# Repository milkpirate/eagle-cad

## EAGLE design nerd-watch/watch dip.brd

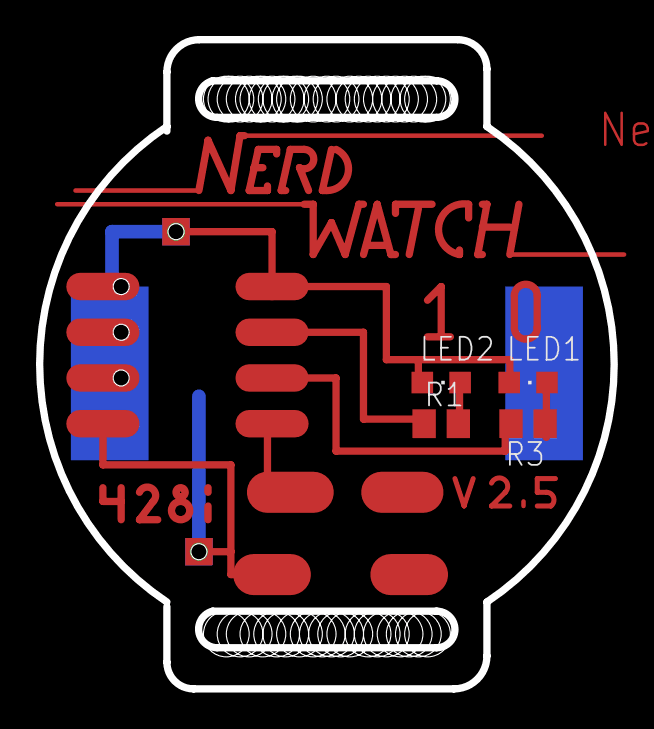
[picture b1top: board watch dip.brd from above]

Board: 2 copper layers, 31.9 x 36.1 mm, 4 parts (0 on the bottom side), 3 nets.

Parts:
LED1, LED2: CHIPLED_0805
R1, R3: M0805

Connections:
3.3V: LED1.A, LED2.A
unnamed: LED2.C, R1.2
unnamed: LED1.C, R3.2

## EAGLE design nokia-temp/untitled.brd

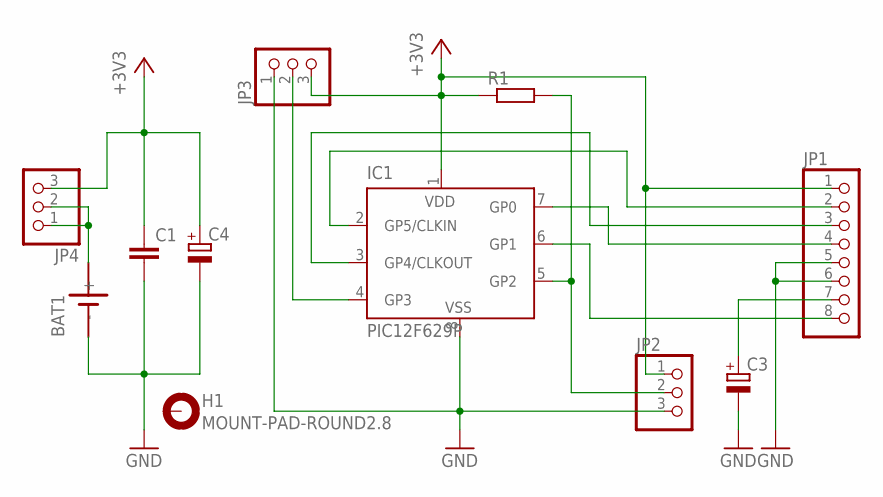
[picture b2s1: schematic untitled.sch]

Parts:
BAT1: SN2032
C1: C-EU025-025X050; C025-025X050
C3, C4: CPOL-EUTT2D5L; TT2D5L
H1: MOUNT-PAD-ROUND2.8; 2,8-PAD
IC1: PIC12F629P; DIL8
JP1: PINHD-1X8; 1X08
JP2, JP3, JP4: PINHD-1X3; 1X03
R1: R-EU_0204/2V; 0204V

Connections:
+3V3: C1.1, C4.+, IC1.1 (VDD), JP1.1, JP2.1, JP3.3, JP4.3, R1.1
GND: BAT1.-, C1.2, C3.-, C4.-, IC1.8 (VSS), JP1.5, JP1.6, JP2.3, JP3.1
unnamed: IC1.6 (GP1), JP1.8
unnamed: IC1.7 (GP0), JP1.4
unnamed: IC1.2 (GP5/CLKIN), JP1.2
unnamed: IC1.3 (GP4/CLKOUT), JP1.3
unnamed: IC1.4 (GP3), JP3.2
unnamed: BAT1.+, JP4.1, JP4.2
unnamed: C3.+, JP1.7
unnamed: IC1.5 (GP2), JP2.2, R1.2

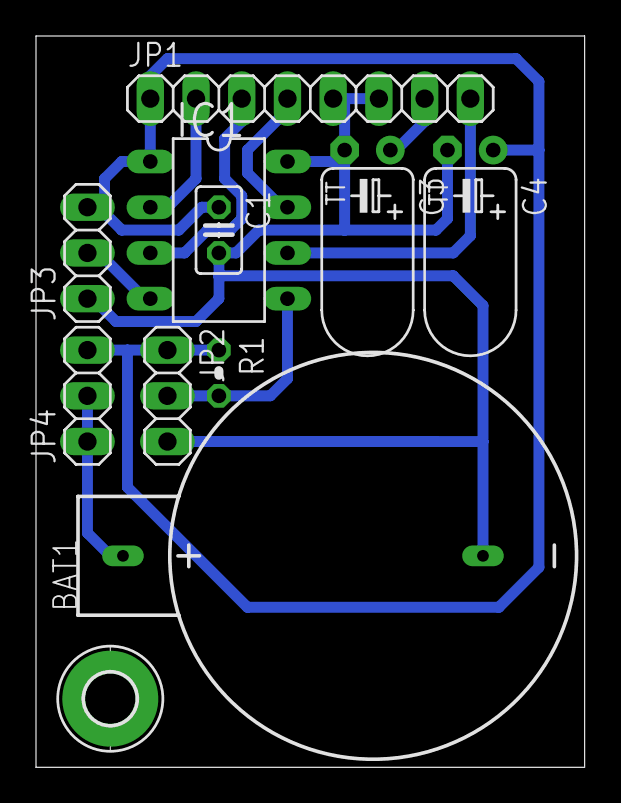
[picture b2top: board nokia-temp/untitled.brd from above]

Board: 2 copper layers, 30.5 x 40.6 mm, 11 parts (0 on the bottom side), 10 nets.

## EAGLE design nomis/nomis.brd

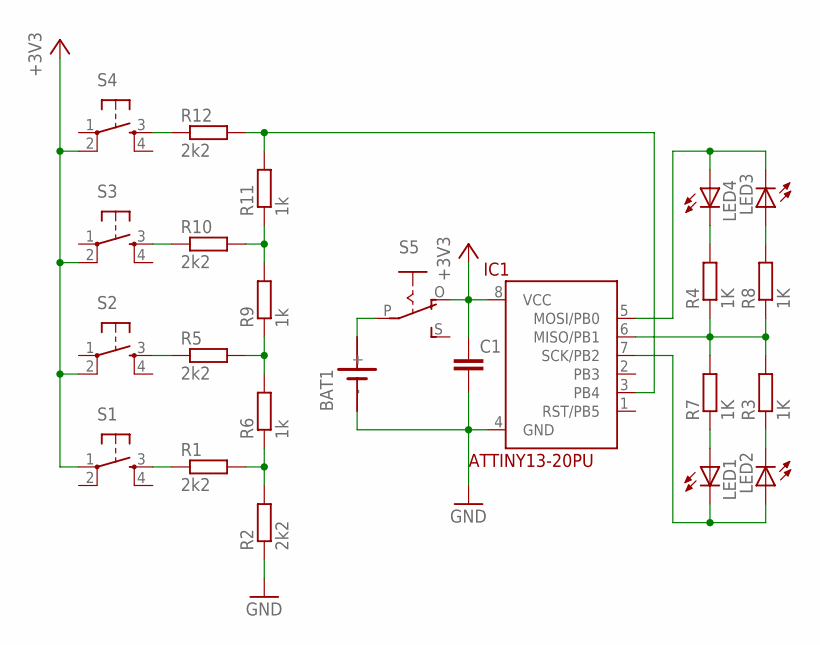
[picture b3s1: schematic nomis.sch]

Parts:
BAT1: SN2032
C1: C-EU025-025X050; C025-025X050
IC1: ATTINY13-20PU; DIL08
LED1, LED2, LED3, LED4: LED5MM
R1, R2, R5, R10, R12: 2k2; 0207/7
R3, R4, R7, R8: 1K; 0207/7
R6, R9, R11: 1k; 0207/7
S1, S2, S3, S4: TAC_SWITCHPTH; TACTILE-PTH
S5: EG1218S; EG1218

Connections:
+3V3: C1.1, IC1.8 (VCC), S1.1, S2.2, S3.2, S4.2, S5.O
GND: BAT1.-, C1.2, IC1.4 (GND), R2.1
unnamed: R10.1, S3.3
unnamed: R5.1, S2.3
unnamed: BAT1.+, S5.P
unnamed: LED2.K (C), R3.1
unnamed: LED4.K (C), R4.2
unnamed: LED1.A, R7.1
unnamed: IC1.6 (MISO/PB1), R3.2, R4.1, R7.2, R8.1
unnamed: IC1.7 (SCK/PB2), LED1.K (C), LED2.A
unnamed: IC1.5 (MOSI/PB0), LED3.K (C), LED4.A
unnamed: LED3.A, R8.2
unnamed: R12.1, S4.3
unnamed: IC1.3 (PB4), R11.2, R12.2
unnamed: R9.2, R10.2, R11.1
unnamed: R5.2, R6.2, R9.1
unnamed: R1.2, R2.2, R6.1
unnamed: R1.1, S1.3

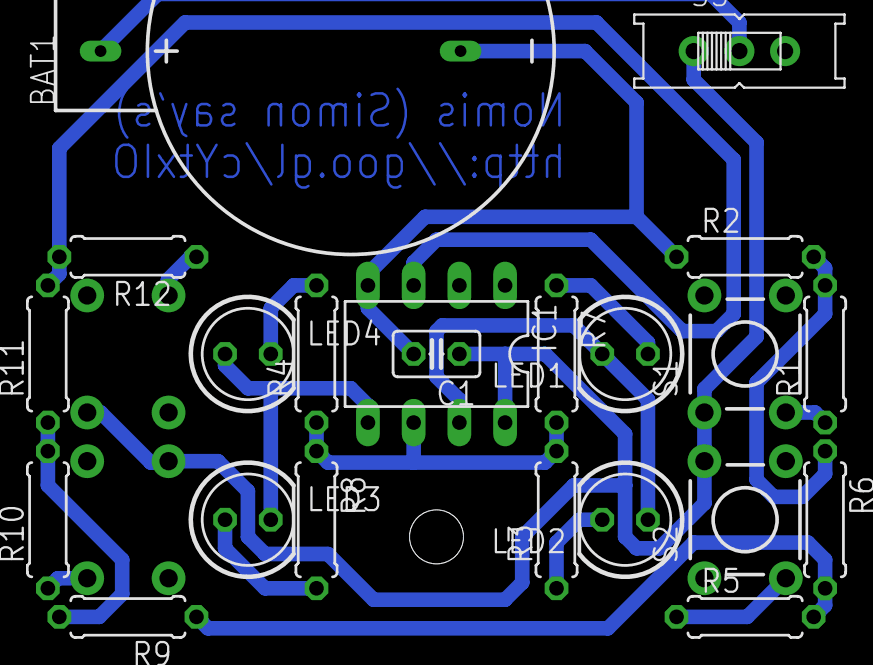
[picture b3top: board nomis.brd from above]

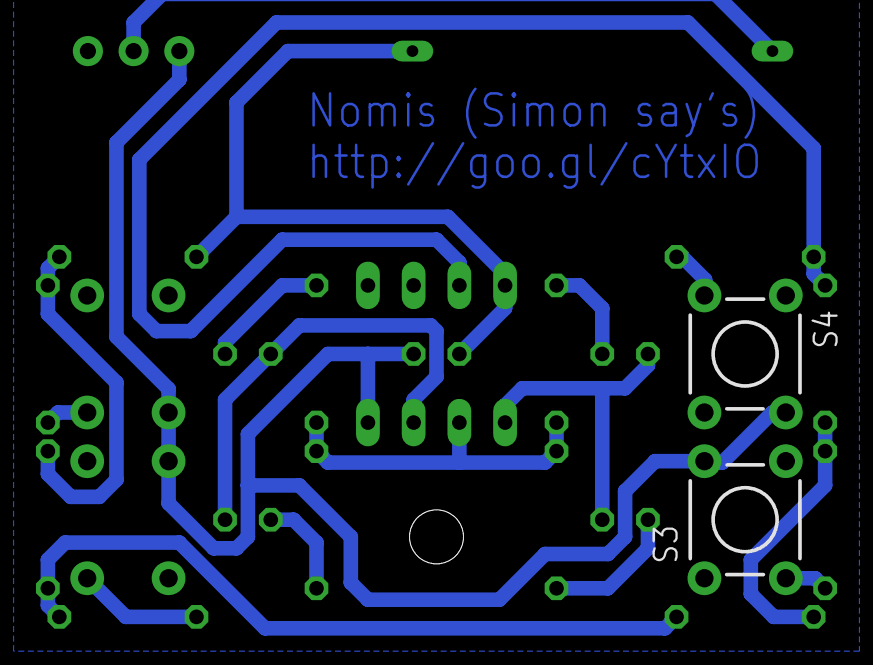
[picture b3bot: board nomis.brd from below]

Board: 2 copper layers, 24 parts (2 on the bottom side), 18 nets.

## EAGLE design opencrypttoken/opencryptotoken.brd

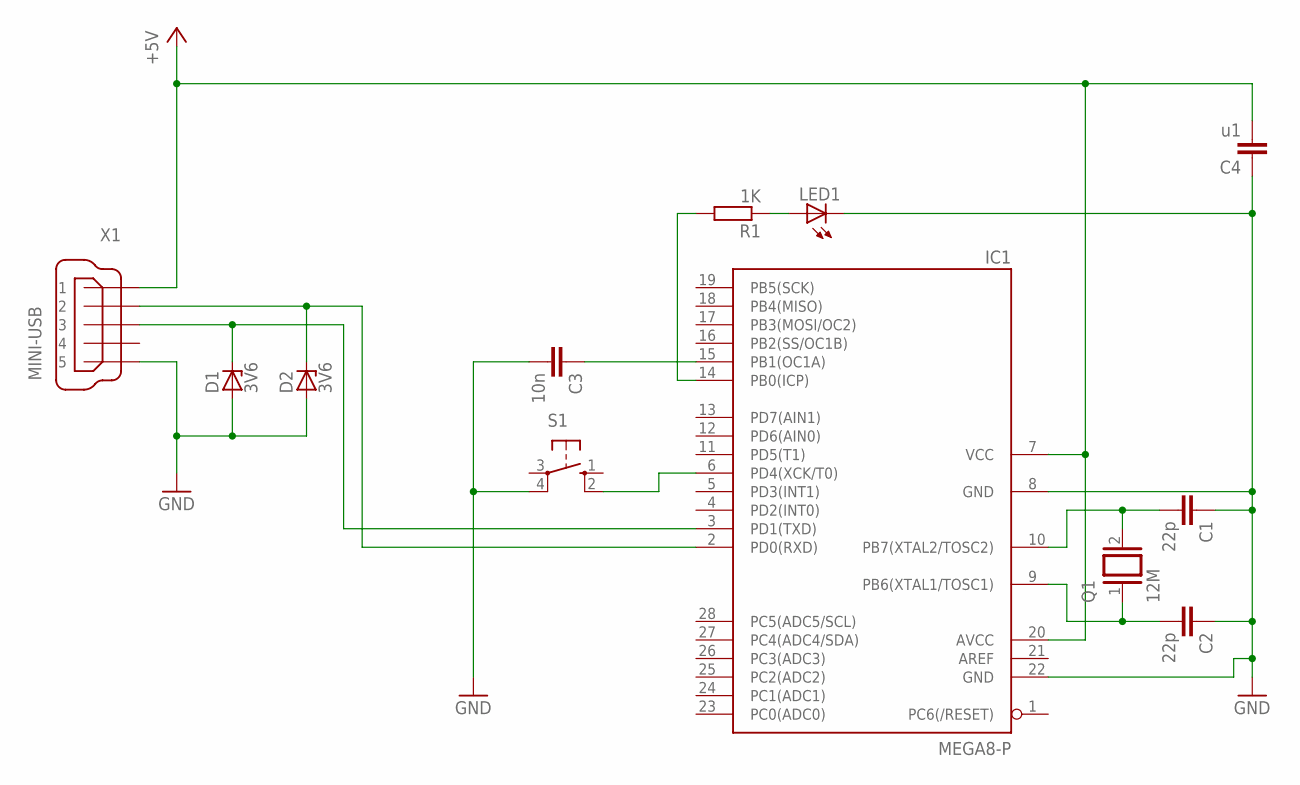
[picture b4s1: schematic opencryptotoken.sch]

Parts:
C1, C2: 22p; C025-024X044
C3: 10n; C025-024X044
C4: u1; C025-024X044
D1: 3V6; ZDIO-2.5
D2: 3V6; ZDIO-5
IC1: MEGA8-P; DIL28-3
LED1: LED5MM
Q1: 12M; QS
R1: 1K; 0204V
S1: 10-XX; B3F-10XX
X1: MINI-USB; 32005-601

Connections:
+5V: C4.2, IC1.7 (VCC), IC1.20 (AVCC), X1.1
GND: C1.1, C2.1, C3.2, C4.1, D1.A, D2.A, IC1.8 (GND), IC1.22 (GND), LED1.K (C), S1.4 (P1), X1.5
unnamed: C1.2, IC1.10 (PB7(XTAL2/TOSC2)), Q1.2
unnamed: C2.2, IC1.9 (PB6(XTAL1/TOSC1)), Q1.1
unnamed: C3.1, IC1.15 (PB1(OC1A))
unnamed: IC1.14 (PB0(ICP)), R1.2
unnamed: LED1.A, R1.1
unnamed: D2.C, IC1.2 (PD0(RXD)), X1.2
unnamed: D1.C, IC1.3 (PD1(TXD)), X1.3
unnamed: IC1.6 (PD4(XCK/T0)), S1.2 (S1)

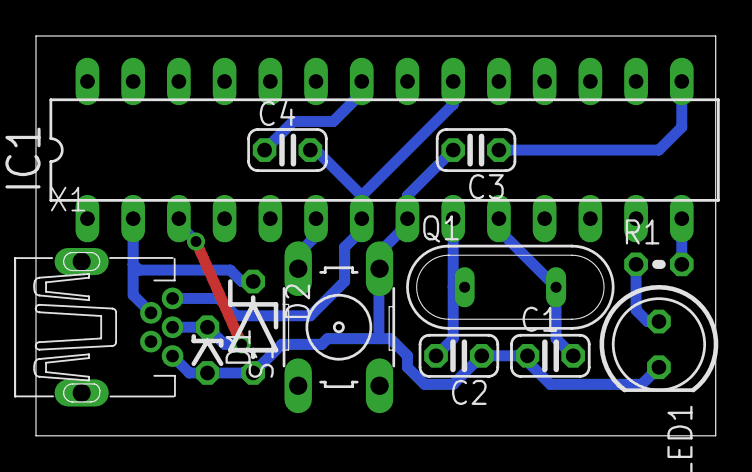
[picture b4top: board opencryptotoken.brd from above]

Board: 2 copper layers, 37.8 x 22.2 mm, 12 parts (0 on the bottom side), 10 nets.

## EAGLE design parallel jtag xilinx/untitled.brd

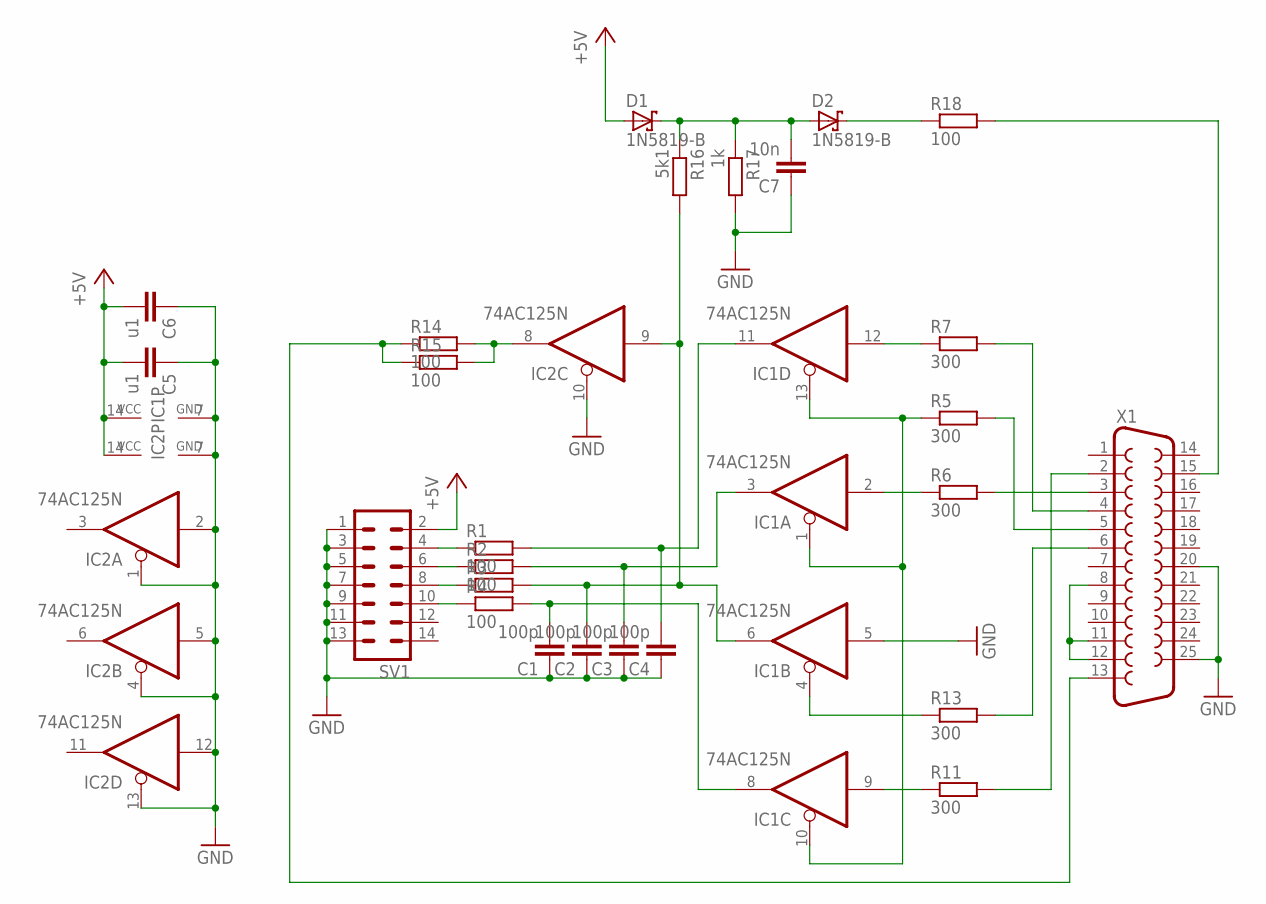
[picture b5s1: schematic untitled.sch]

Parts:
C1, C2, C3, C4: 100p; C025-025X050
C5, C6: u1; C025-025X050
C7: 10n; C025-025X050
D1, D2: 1N5819-B; DO41-7.6
IC1, IC2: 74AC125N; DIL14
R1, R2, R4, R18: 100; 0207/2V
R3: R-EU_0207/2V; 0207/2V
R5, R6, R7, R13: 300; 0207/7
R11: 300; 0207/12
R14, R15: 100; 0207/7
R16: 5k1; 0309/12
R17: 1k; 0207/7
SV1: ML14
X1: F25HP

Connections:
+5V: C5.2, C6.2, D1.A, IC1.14 (VCC), IC2.14 (VCC), SV1.2
GND: C1.1, C2.1, C3.1, C4.1, C5.1, C6.1, C7.1, IC1.5 (I), IC1.7 (GND), IC2.1 (OE), IC2.2 (I), IC2.4 (OE), IC2.5 (I), IC2.7 (GND), IC2.10 (OE), IC2.12 (I), IC2.13 (OE), R17.2, SV1.1, SV1.3, SV1.5, SV1.7, SV1.9, SV1.11, SV1.13, X1.20, X1.25
unnamed: C1.2, IC1.8 (O), R4.2
unnamed: R1.1, SV1.4
unnamed: R2.1, SV1.6
unnamed: R3.1, SV1.8
unnamed: R4.1, SV1.10
unnamed: C2.2, IC1.6 (O), IC2.9 (I), R3.2, R16.2
unnamed: C3.2, IC1.3 (O), R2.2
unnamed: C4.2, IC1.11 (O), R1.2
unnamed: IC1.1 (OE), IC1.10 (OE), IC1.13 (OE), R5.1
unnamed: IC1.12 (I), R7.1
unnamed: IC1.9 (I), R11.1
unnamed: IC1.4 (OE), R13.1
unnamed: IC1.2 (I), R6.1
unnamed: IC2.8 (O), R14.2, R15.2
unnamed: R14.1, R15.1, X1.13
unnamed: C7.2, D1.C, D2.A, R16.1, R17.1
unnamed: D2.C, R18.1
unnamed: R18.2, X1.15
unnamed: R7.2, X1.4
unnamed: R5.2, X1.5
unnamed: R6.2, X1.3
unnamed: R13.2, X1.6
unnamed: R11.2, X1.2
unnamed: X1.8, X1.11, X1.12

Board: 2 copper layers, 27 parts (0 on the bottom side), 26 nets, no tracks yet.

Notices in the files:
parts and their libraries:
SparkFun: Licensing: CC v3.0 Share-Alike You are welcome to use this library for commercial purposes.
